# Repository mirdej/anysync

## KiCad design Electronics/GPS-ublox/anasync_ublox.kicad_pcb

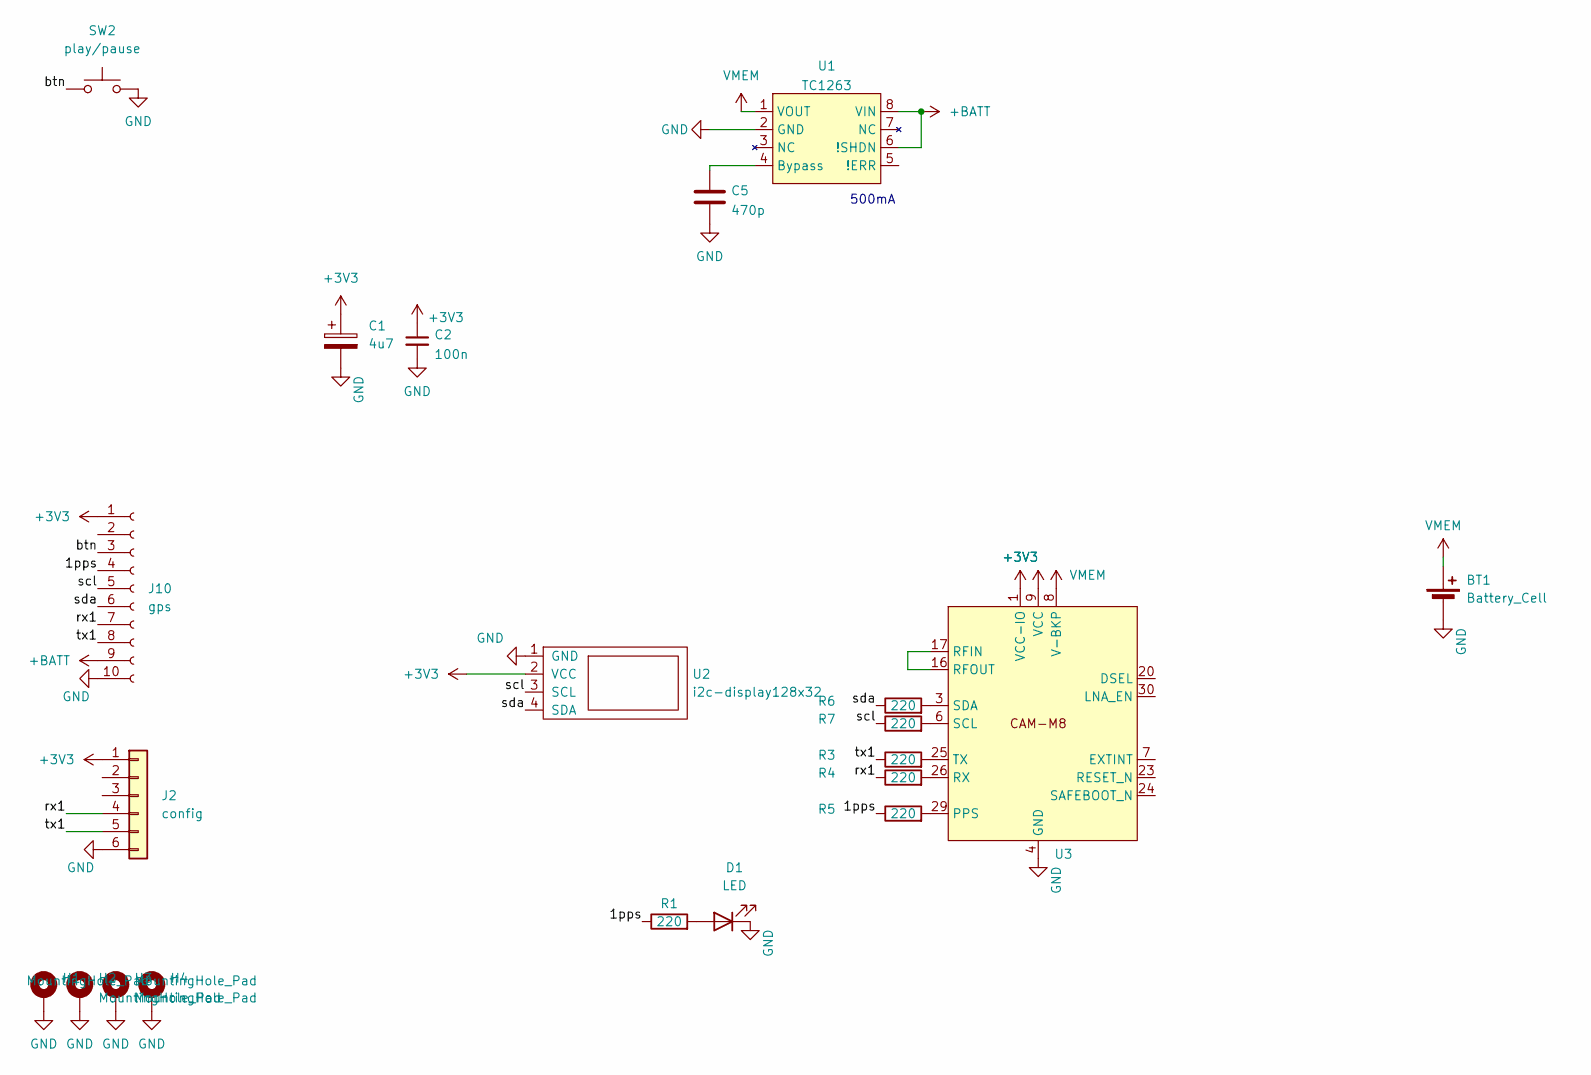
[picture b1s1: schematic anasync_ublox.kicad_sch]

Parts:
BT1: Battery_Cell; ComboPinhead_02
C1: 4u7; C_1206_3216Metric_Pad1.42x1.75mm_HandSolder
C2: 100n; C_0603_1608Metric_Pad1.05x0.95mm_HandSolder
C5: 470p; C_0805_2012Metric_Pad1.15x1.40mm_HandSolder
D1: LED; LED_D3.0mm_Clear
H1, H2, H3, H4: MountingHole_Pad; MountingHole_2.7mm_M2.5_DIN965_Pad
J2: config; ComboPinhead_06
J10: gps; ComboPinhead_10
R1, R3, R4, R5, R6, R7: 220; C_0805_2012Metric_Pad1.15x1.40mm_HandSolder
SW2: play/pause; Alps_Tactile_Switch
U1: TC1263; SOIC-8_3.9x4.9mm_P1.27mm
U2: i2c-display128x32; Bangood_I2C_Display
U3: CAM-M8

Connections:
+3V3: C1.1, C2.1, J2.1, J10.1, U2.2 (VCC), U3.1 (VCC-IO), U3.9 (VCC)
+BATT: J10.9, U1.6 (!SHDN), U1.8 (VIN)
/1pps: J10.4, R1.1, R5.1
/btn: J10.3, SW2.1
/rx1: J2.4, J10.7, R4.1
/scl: J10.5, R7.1, U2.3 (SCL)
/sda: J10.6, R6.1, U2.4 (SDA)
/tx1: J2.5, J10.8, R3.1
GND: BT1.2 (-), C1.2, C2.2, C5.2, D1.1 (K), H1.1, H2.1, H3.1, H4.1, J2.6, J10.10, SW2.2, U1.2 (GND), U2.1 (GND), U3.4 (GND), U3.5 (GND), U3.10 (GND), U3.11 (GND), U3.12 (GND), U3.13 (GND), U3.14 (GND), U3.15 (GND), U3.18 (GND), U3.19 (GND), U3.21 (GND), U3.22 (GND), U3.27 (GND), U3.31 (GND)
unnamed: D1.2 (A), R1.2
unnamed: C5.1, U1.4 (Bypass)
unnamed: R5.2, U3.29 (PPS)
unnamed: U3.16 (RFOUT), U3.17 (RFIN)
unnamed: R4.2, U3.26 (RX)
unnamed: R7.2, U3.6 (SCL)
unnamed: R6.2, U3.3 (SDA)
unnamed: R3.2, U3.25 (TX)
VMEM: BT1.1 (+), U1.1 (VOUT), U3.8 (V-BKP)

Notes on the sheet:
500mA

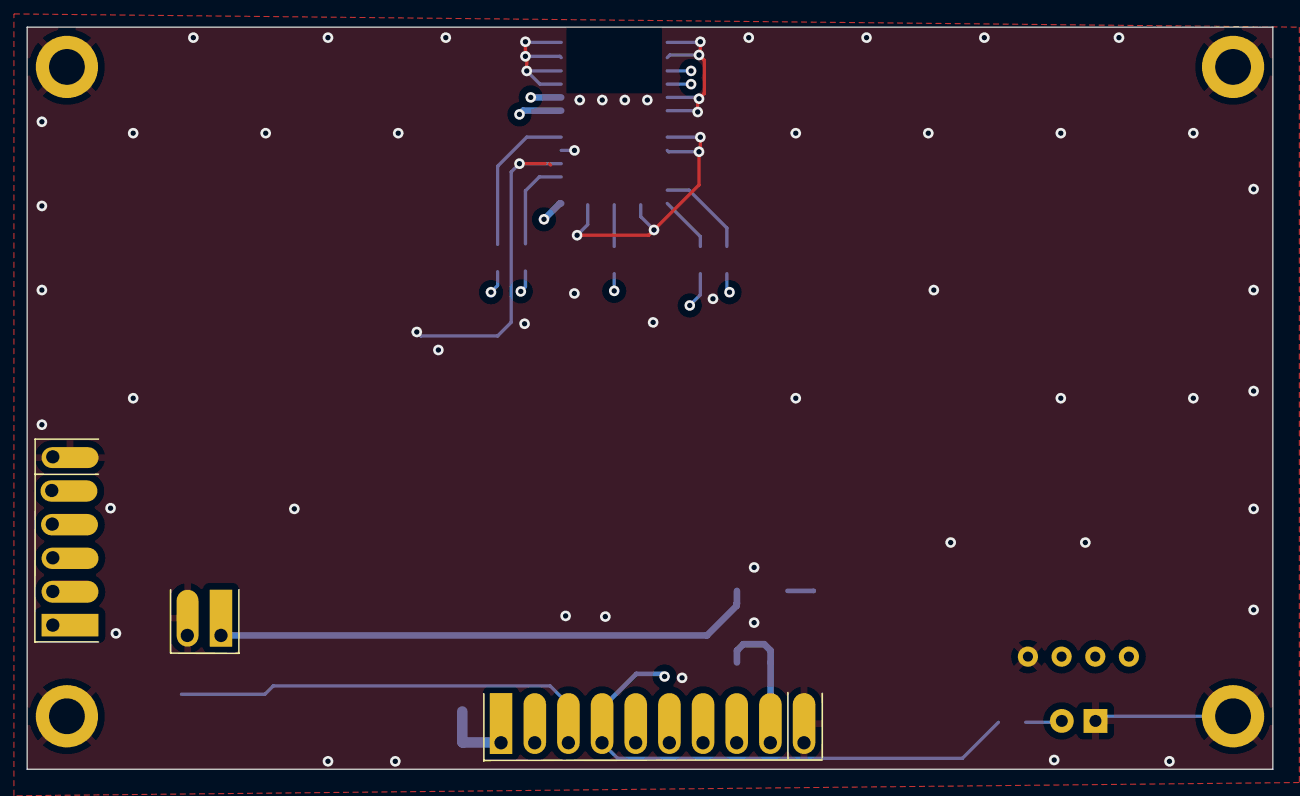
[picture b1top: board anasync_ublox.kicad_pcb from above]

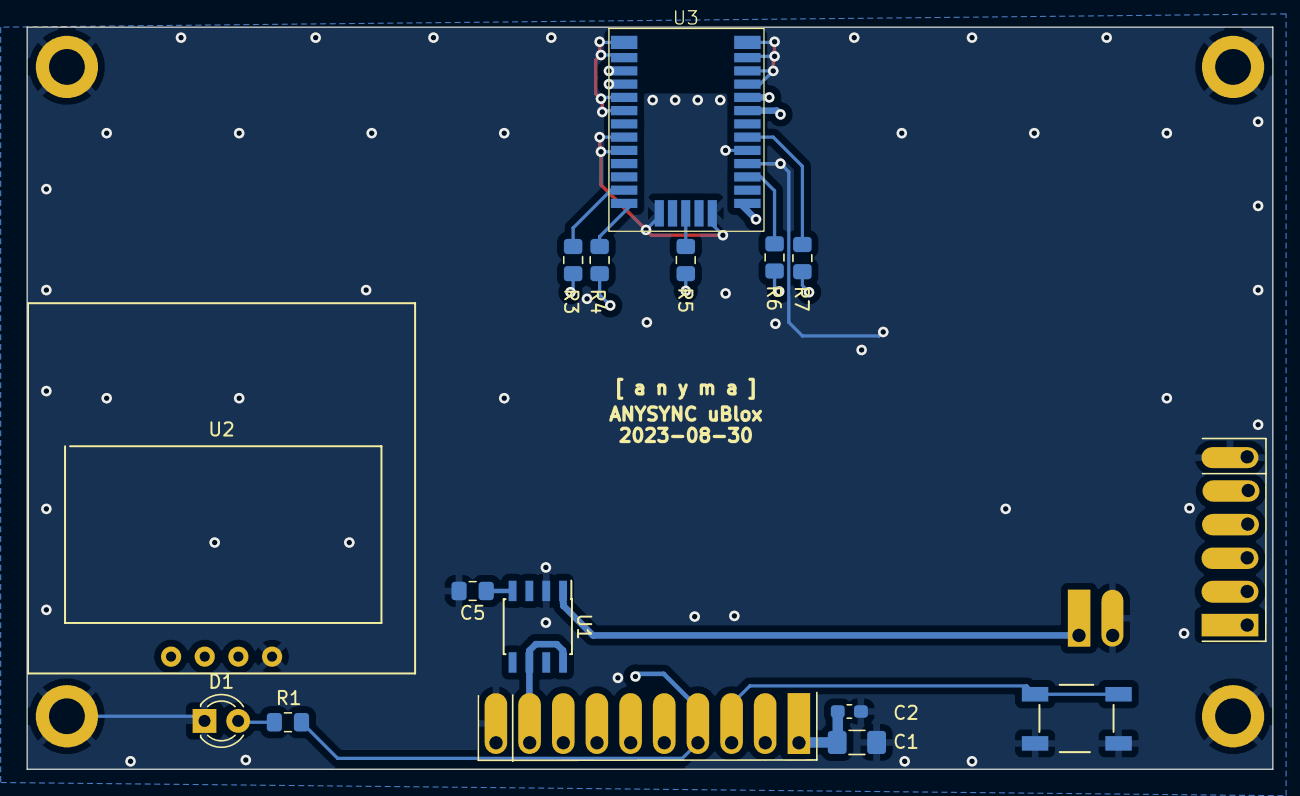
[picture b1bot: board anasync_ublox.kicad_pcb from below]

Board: 4 copper layers, 94.0 x 56.0 mm, 21 parts (15 on the bottom side), 18 nets.

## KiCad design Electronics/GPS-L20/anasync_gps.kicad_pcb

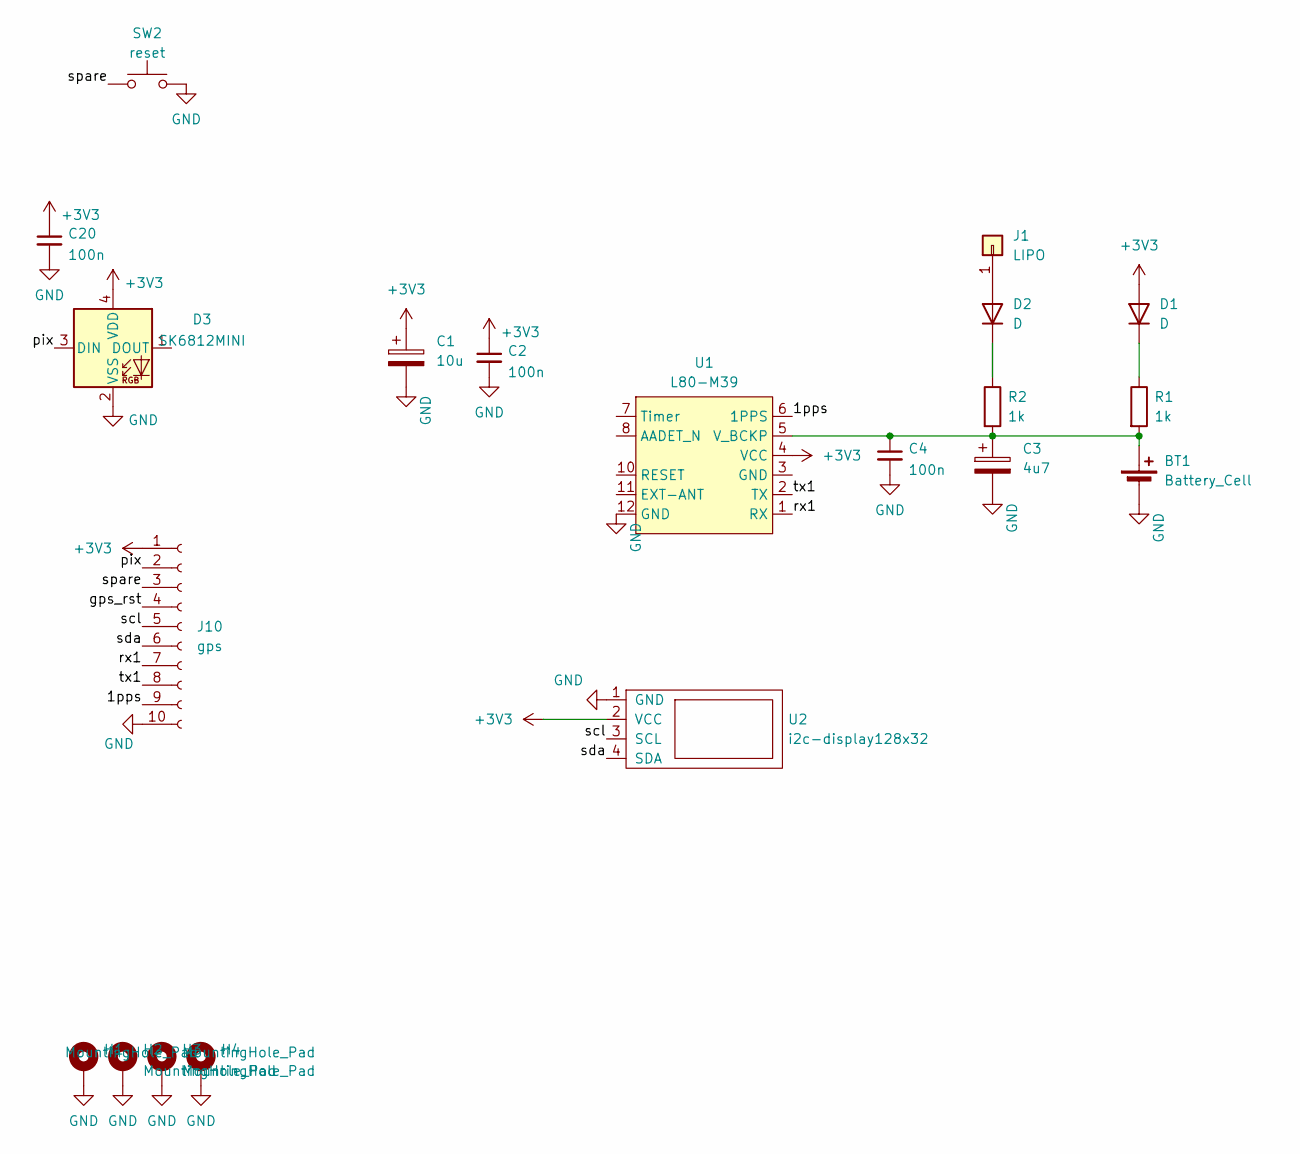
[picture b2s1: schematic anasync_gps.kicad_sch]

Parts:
BT1: Battery_Cell; smd-2pin
C1: 10u; C_1206_3216Metric_Pad1.42x1.75mm_HandSolder
C2, C4, C20: 100n; C_0603_1608Metric_Pad1.05x0.95mm_HandSolder
C3: 4u7; C_1206_3216Metric_Pad1.42x1.75mm_HandSolder
D1, D2: D; D_MiniMELF_Handsoldering
D3: SK6812MINI; SK6812-MINI-HS
H1, H2, H3, H4: MountingHole_Pad; MountingHole_2.2mm_M2_DIN965_Pad
J1: LIPO; smd-1pin
J10: gps; ComboPinhead_10
R1, R2: 1k; C_0805_2012Metric_Pad1.15x1.40mm_HandSolder
SW2: reset; Alps_Tactile_Switch
U1: L80-M39
U2: i2c-display128x32; Bangood_I2C_Display

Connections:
+3V3: C1.1, C2.1, C20.1, D1.2 (A), D3.4 (VDD), J10.1, U1.4 (VCC), U2.2 (VCC)
/1pps: J10.9, U1.6 (1PPS)
/gps_rst: J10.4
/pix: D3.3 (DIN), J10.2
/rx1: J10.7, U1.1 (RX)
/scl: J10.5, U2.3 (SCL)
/sda: J10.6, U2.4 (SDA)
/spare: J10.3, SW2.1
/tx1: J10.8, U1.2 (TX)
GND: BT1.2 (-), C1.2, C2.2, C3.2, C4.2, C20.2, D3.2 (VSS), H1.1, H2.1, H3.1, H4.1, J10.10, SW2.2, U1.12 (GND), U2.1 (GND)
unnamed: BT1.1 (+), C3.1, C4.1, R1.2, R2.2, U1.5 (V_BCKP)
unnamed: D1.1 (K), R1.1
unnamed: D2.2 (A), J1.1
unnamed: D2.1 (K), R2.1

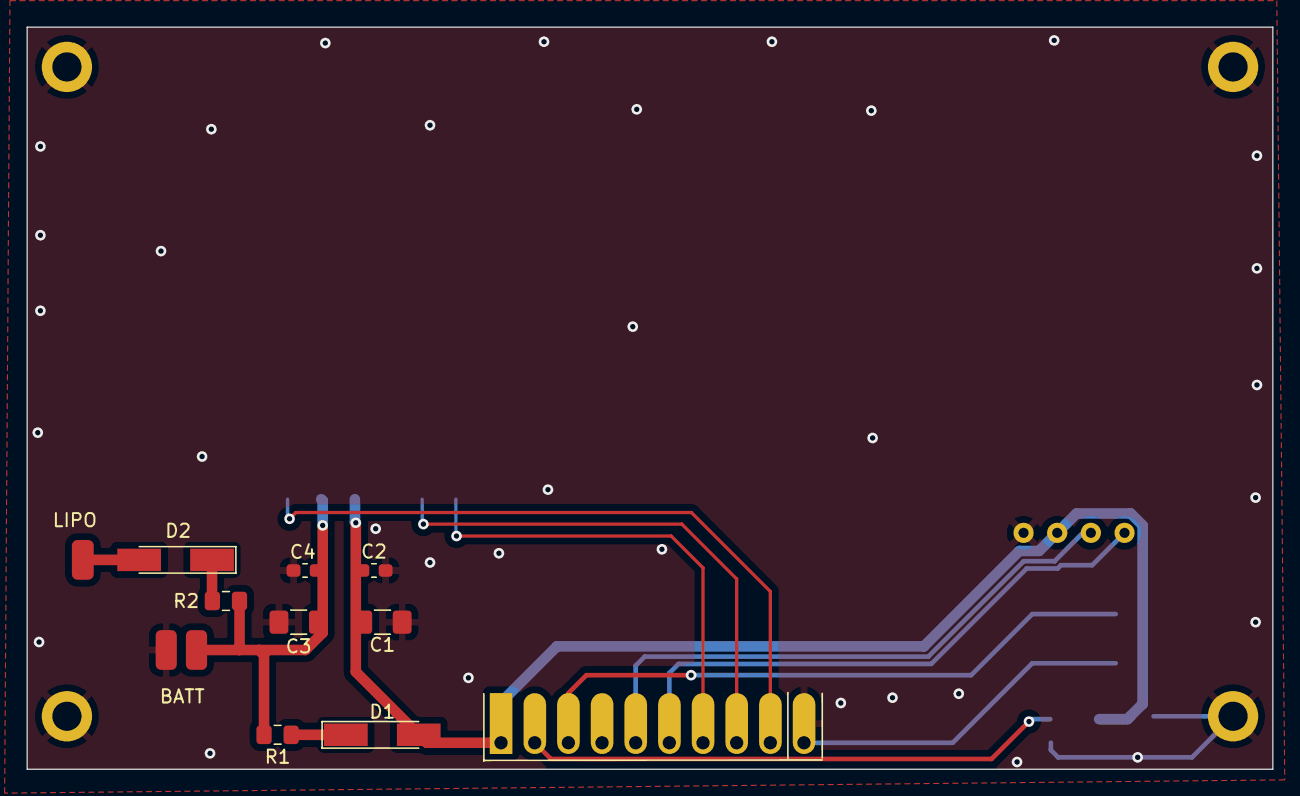
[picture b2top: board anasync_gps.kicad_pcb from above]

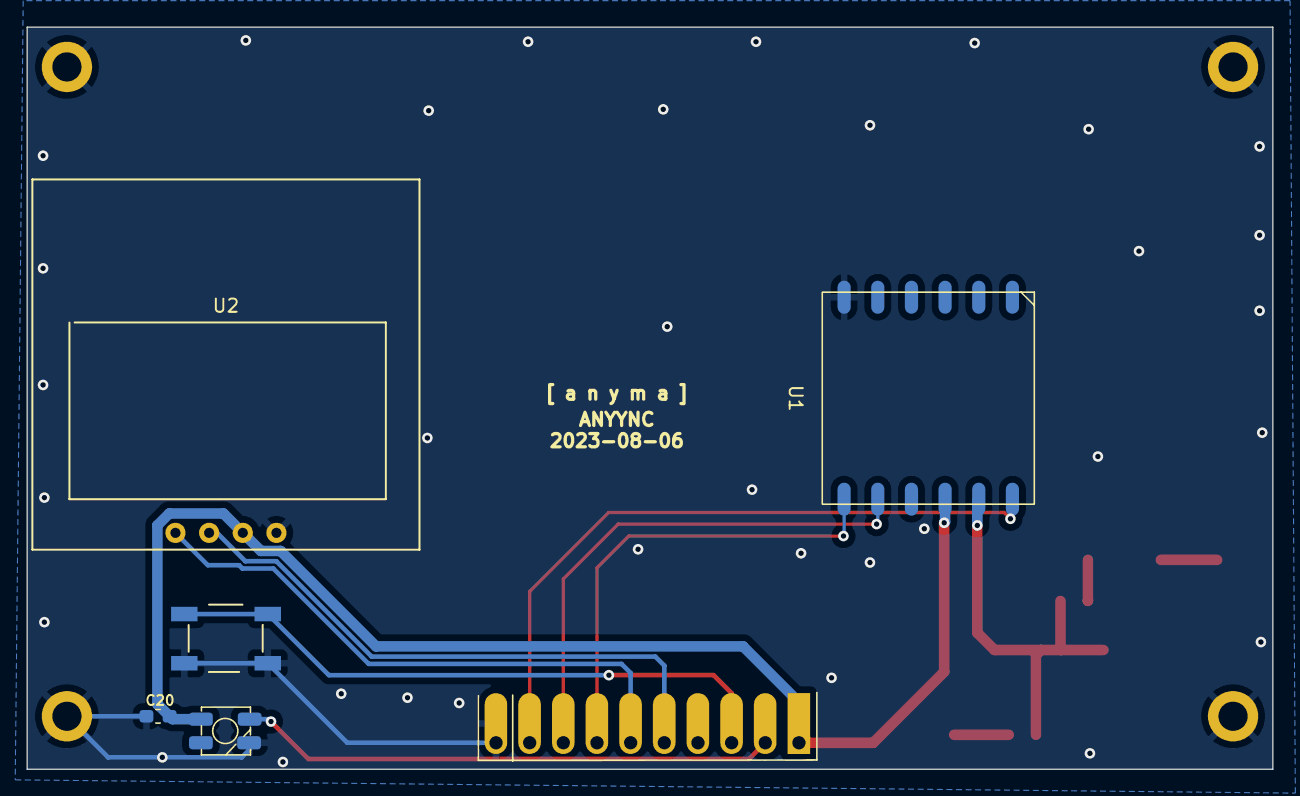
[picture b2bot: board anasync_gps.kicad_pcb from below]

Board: 2 copper layers, 94.0 x 56.0 mm, 20 parts (6 on the bottom side), 13 nets.

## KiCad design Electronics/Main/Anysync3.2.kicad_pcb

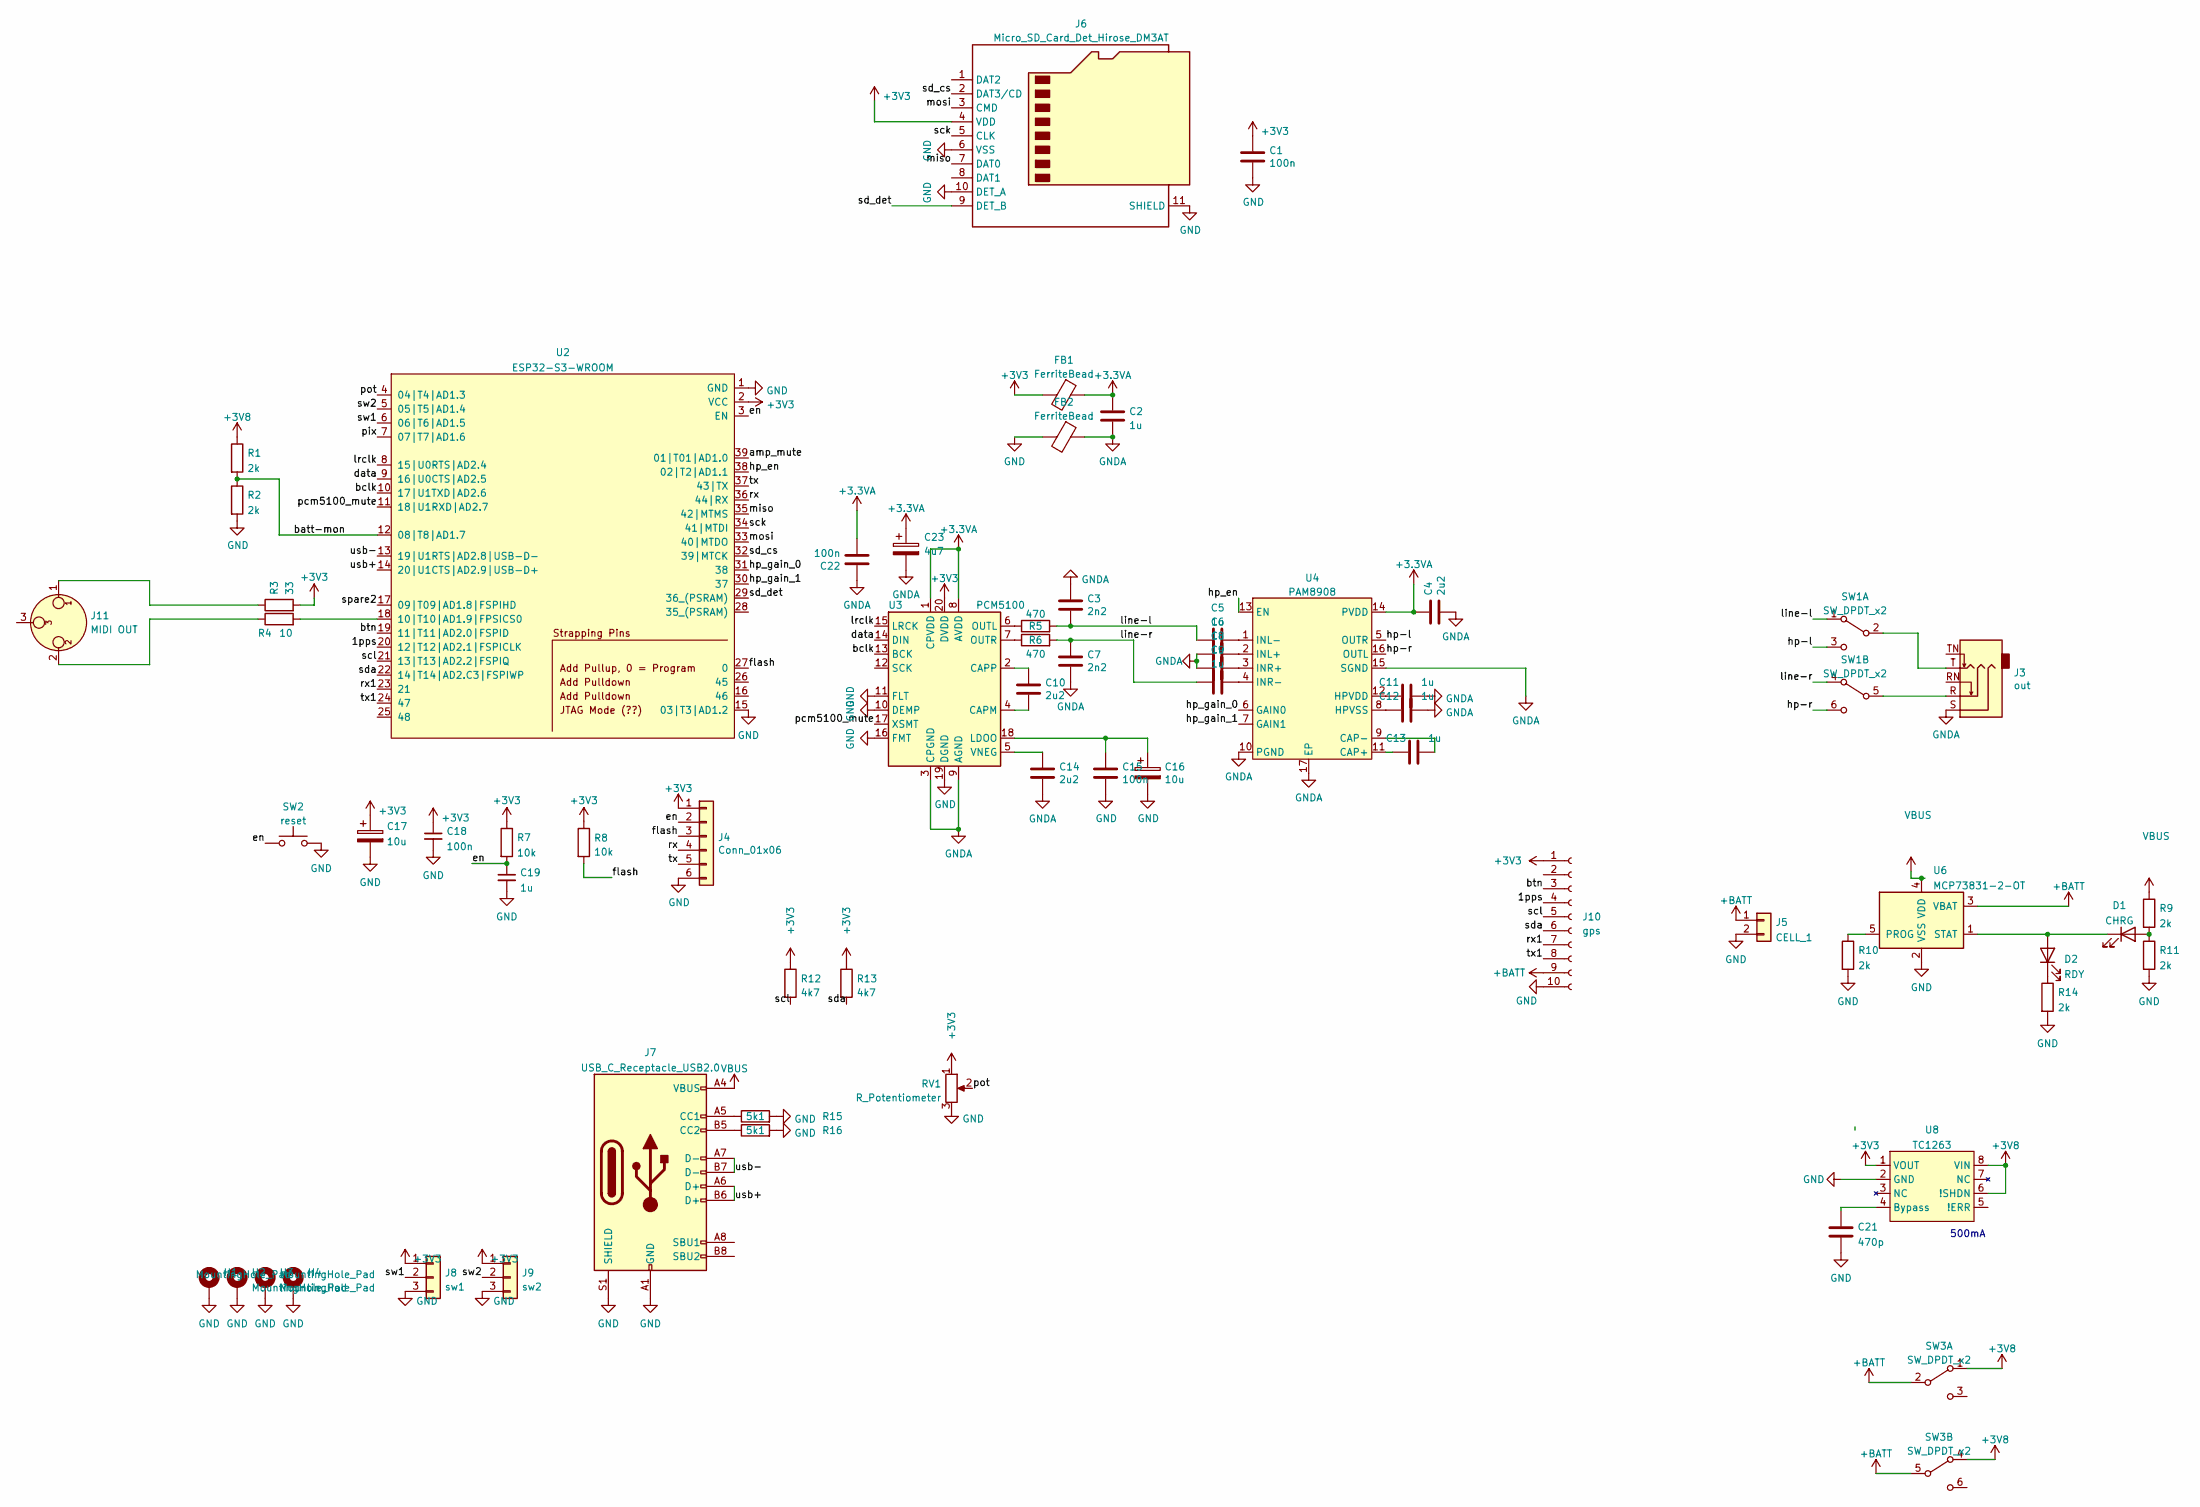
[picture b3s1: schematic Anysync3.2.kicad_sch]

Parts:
C1, C15, C18, C22: 100n; C_0603_1608Metric_Pad1.05x0.95mm_HandSolder
C2, C5, C6, C8, C9, C11, C12, C13, C19: 1u; C_0603_1608Metric_Pad1.05x0.95mm_HandSolder
C3, C7: 2n2; C_0805_2012Metric_Pad1.15x1.40mm_HandSolder
C4: 2u2; C_0805_2012Metric_Pad1.15x1.40mm_HandSolder
C10, C14: 2u2; C_1206_3216Metric_Pad1.42x1.75mm_HandSolder
C16: 10u; CP_EIA-3528-21_Kemet-B_Pad1.50x2.35mm_HandSolder
C17: 10u; C_1206_3216Metric_Pad1.42x1.75mm_HandSolder
C21: 470p; C_0805_2012Metric_Pad1.15x1.40mm_HandSolder
C23: 4u7; C_1206_3216Metric_Pad1.42x1.75mm_HandSolder
D1: CHRG; LED_0805_2012Metric
D2: RDY; LED_0805_2012Metric
FB1, FB2: FerriteBead; L_0805_2012Metric_Pad1.15x1.40mm_HandSolder
H1, H2, H3, H4: MountingHole_Pad; MountingHole_2.7mm_M2.5_DIN965_Pad
J3: out; Jack_3.5mm_SMD
J4: Conn_01x06; AnymaPOGO-ESP
J5: CELL_1; JST_XH_B2B-XH-AM_1x02_P2.50mm_Vertical
J6: Micro_SD_Card_Det_Hirose_DM3AT; microSD_HC_Hirose_DM3BT-DSF-PEJS
J7: USB_C_Receptacle_USB2.0; JAE_USB-C_SJ122205
J8: sw1; ComboPinhead_03
J9: sw2; ComboPinhead_03
J10: gps; ComboPinhead_10
J11: MIDI OUT; TRAPC3MSX
R1, R2, R9, R10, R11, R14: 2k; R_0805_2012Metric_Pad1.15x1.40mm_HandSolder
R3: 33; R_0805_2012Metric_Pad1.15x1.40mm_HandSolder
R4: 10; R_0805_2012Metric_Pad1.15x1.40mm_HandSolder
R5, R6: 470; R_0805_2012Metric_Pad1.15x1.40mm_HandSolder
R7, R8: 10k; R_0805_2012Metric_Pad1.15x1.40mm_HandSolder
R12, R13: 4k7; R_0805_2012Metric_Pad1.15x1.40mm_HandSolder
R15, R16: 5k1; R_0805_2012Metric_Pad1.15x1.40mm_HandSolder
RV1: R_Potentiometer; RK10J12E
SW1, SW3: SW_DPDT_x2; JS202011SCQN
SW2: reset; Alps_Tactile_Switch
U2: ESP32-S3-WROOM
U3: PCM5100; TSSOP-20_4.4x6.5mm_P0.65mm
U4: PAM8908; QFN-16-1EP_3x3mm_P0.5mm_EP1.7x1.7mm
U6: MCP73831-2-OT; SOT-23-5
U8: TC1263; SOIC-8_3.9x4.9mm_P1.27mm

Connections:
+3.3VA: C2.1, C4.1, C22.2, C23.1, FB1.1, U3.1 (CPVDD), U3.8 (AVDD), U4.14 (PVDD)
+3V3: C1.1, C17.1, C18.1, FB1.2, J4.1, J6.4 (VDD), J8.1, J9.1, J10.1, R3.2, R7.1, R8.1, R12.1, R13.1, RV1.1, U2.2 (VCC), U3.20 (DVDD), U8.1 (VOUT)
+3V8: R1.1, SW3.1 (A), SW3.4 (A), U8.6 (!SHDN), U8.8 (VIN)
+BATT: J5.1, J10.9, SW3.2 (B), SW3.5 (B), U6.3 (VBAT)
/1pps: J10.4, U2.20 (12|T12|AD2.1|FSPICLK)
/amp_mute: U2.39 (01|T01|AD1.0)
/batt-mon: R1.2, R2.1, U2.12 (08|T8|AD1.7)
/bclk: U2.10 (17|U1TXD|AD2.6), U3.13 (BCK)
/btn: J10.3, U2.19 (11|T11|AD2.0|FSPID)
/data: U2.9 (16|U0CTS|AD2.5), U3.14 (DIN)
/en: C19.1, J4.2, R7.2, SW2.1, U2.3 (EN)
/flash: J4.3, R8.2, U2.27 (0)
/hp-l: SW1.3 (C), U4.5 (OUTR)
/hp-r: SW1.6 (C), U4.16 (OUTL)
/hp_en: U2.38 (02|T2|AD1.1), U4.13 (EN)
/hp_gain_0: U2.31 (38), U4.6 (GAIN0)
/hp_gain_1: U2.30 (37), U4.7 (GAIN1)
/line-l: C3.2, C5.1, R5.2, SW1.1 (A)
/line-r: C7.1, C9.1, R6.2, SW1.4 (A)
/lrclk: U2.8 (15|U0RTS|AD2.4), U3.15 (LRCK)
/miso: J6.7 (DAT0), U2.35 (42|MTMS)
/mosi: J6.3 (CMD), U2.33 (40|MTDO)
/pcm5100_mute: U2.11 (18|U1RXD|AD2.7), U3.17 (XSMT)
/pix: U2.7 (07|T7|AD1.6)
/pot: RV1.2, U2.4 (04|T4|AD1.3)
/rx: J4.4, U2.36 (44|RX)
/rx1: J10.7, U2.23 (21)
/sck: J6.5 (CLK), U2.34 (41|MTDI)
/scl: J10.5, R12.2, U2.21 (13|T13|AD2.2|FSPIQ)
/sd_cs: J6.2 (DAT3/CD), U2.32 (39|MTCK)
/sd_det: J6.9 (DET_B), U2.29 (36_(PSRAM))
/sda: J10.6, R13.2, U2.22 (14|T14|AD2.C3|FSPIWP)
/spare2: U2.17 (09|T09|AD1.8|FSPIHD)
/sw1: J8.2, U2.6 (06|T6|AD1.5)
/sw2: J9.2, U2.5 (05|T5|AD1.4)
/tx: J4.5, U2.37 (43|TX)
/tx1: J10.8, U2.24 (47)
/usb+: J7.A6 (D+), J7.B6 (D+), U2.14 (20|U1CTS|AD2.9|USB-D+)
/usb-: J7.A7 (D-), J7.B7 (D-), U2.13 (19|U1RTS|AD2.8|USB-D-)
GND: C1.2, C15.2, C16.2, C17.2, C18.2, C19.2, C21.2, FB2.2, H1.1, H2.1, H3.1, H4.1, J4.6, J5.2, J6.6 (VSS), J6.10 (DET_A), J6.11 (SHIELD), J7.A1 (GND), J7.A12 (GND), J7.B1 (GND), J7.B12 (GND), J7.S1 (SHIELD), J8.3, J9.3, J10.10, R2.2, R10.2, R11.2, R14.2, R15.2, R16.2, RV1.3, SW2.2, U2.1 (GND), U2.15 (03|T3|AD1.2), U2.40 (GND), U2.41 (GND), U3.10 (DEMP), U3.11 (FLT), U3.16 (FMT), U3.19 (DGND), U6.2 (VSS), U8.2 (GND)
GNDA: C2.2, C3.1, C4.2, C6.1, C7.2, C8.1, C11.2, C12.2, C14.2, C22.1, C23.2, FB2.1, J3.S, U3.3 (CPGND), U3.9 (AGND), U4.10 (PGND), U4.15 (SGND), U4.17 (EP)
unnamed: D1.2 (A), R9.2, R11.1
unnamed: D1.1 (K), D2.2 (A), U6.1 (STAT)
unnamed: D2.1 (K), R14.1
unnamed: J7.A5 (CC1), R15.1
unnamed: J7.B5 (CC2), R16.1
unnamed: J11.1, R3.1
unnamed: J11.2, R4.1
unnamed: J3.T, SW1.2 (B)
unnamed: J3.R, SW1.5 (B)
unnamed: R4.2, U2.18 (10|T10|AD1.9|FPSICS0)
unnamed: C10.2, U3.4 (CAPM)
unnamed: C10.1, U3.2 (CAPP)
unnamed: C15.1, C16.1, U3.18 (LDOO)
unnamed: R5.1, U3.6 (OUTL)
unnamed: R6.1, U3.7 (OUTR)
unnamed: C14.1, U3.5 (VNEG)
unnamed: C13.1, U4.11 (CAP+)
unnamed: C13.2, U4.9 (CAP-)
unnamed: C11.1, U4.12 (HPVDD)
unnamed: C12.1, U4.8 (HPVSS)
unnamed: C6.2, U4.2 (INL+)
unnamed: C5.2, U4.1 (INL-)
unnamed: C8.2, U4.3 (INR+)
unnamed: C9.2, U4.4 (INR-)
unnamed: R10.1, U6.5 (PROG)
unnamed: C21.1, U8.4 (Bypass)
VBUS: J7.A4 (VBUS), J7.A9 (VBUS), J7.B4 (VBUS), J7.B9 (VBUS), R9.1, U6.4 (VDD)

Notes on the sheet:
500mA

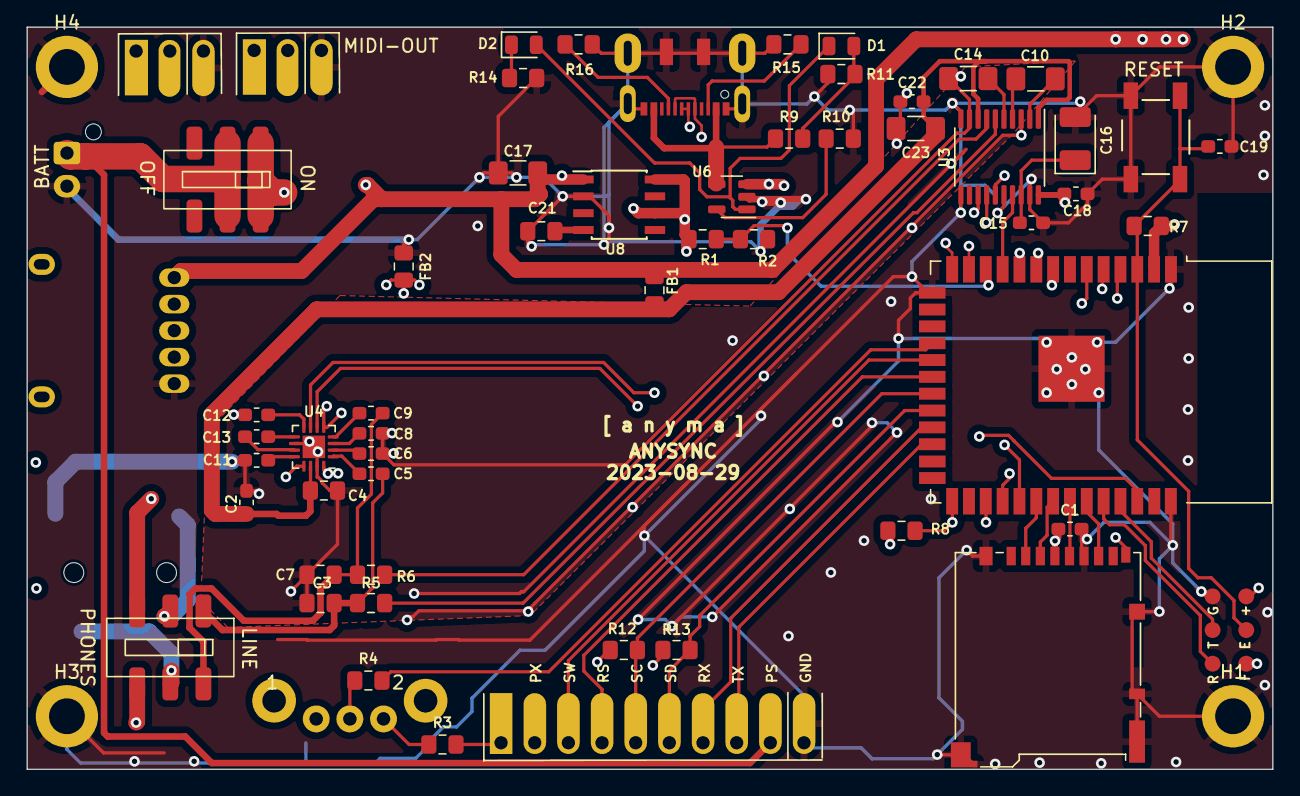
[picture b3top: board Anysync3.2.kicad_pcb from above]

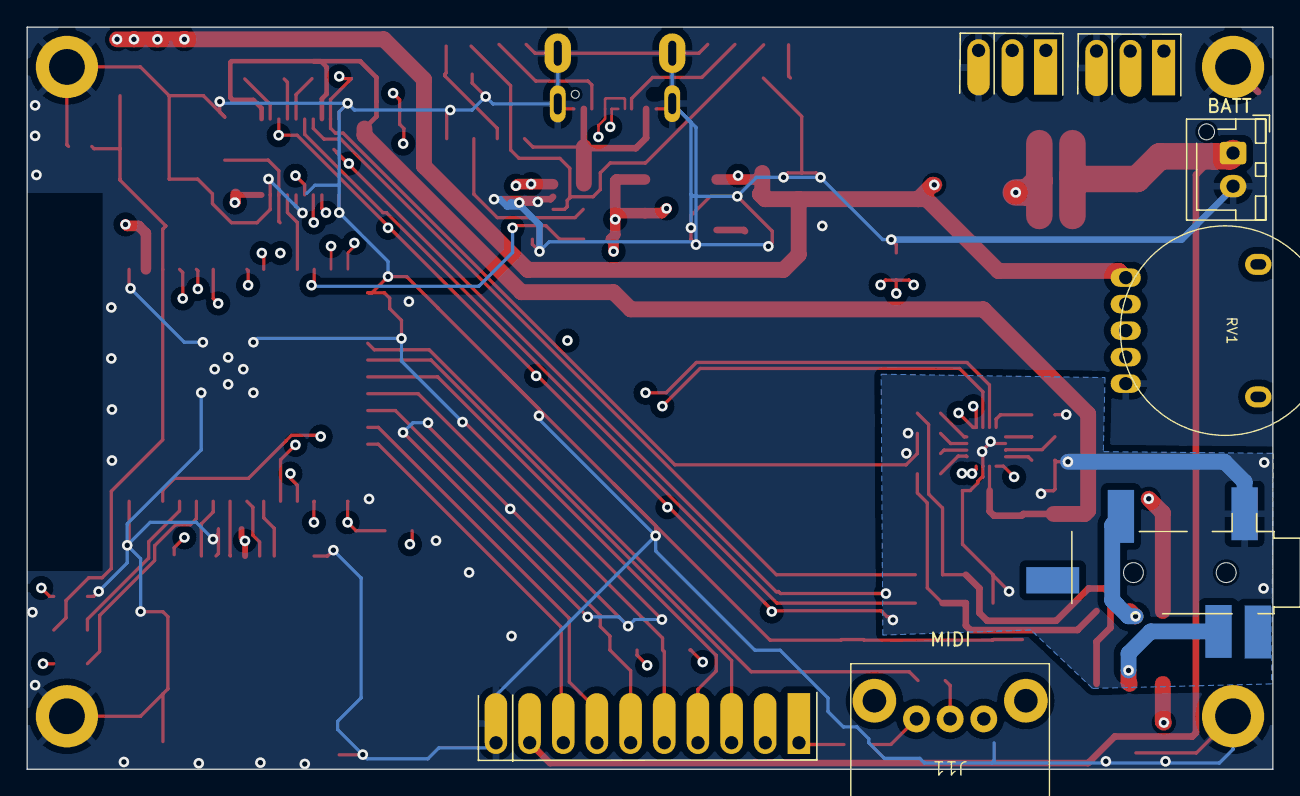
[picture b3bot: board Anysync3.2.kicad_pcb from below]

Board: 4 copper layers, 94.0 x 56.0 mm, 64 parts (5 on the bottom side), 65 nets.

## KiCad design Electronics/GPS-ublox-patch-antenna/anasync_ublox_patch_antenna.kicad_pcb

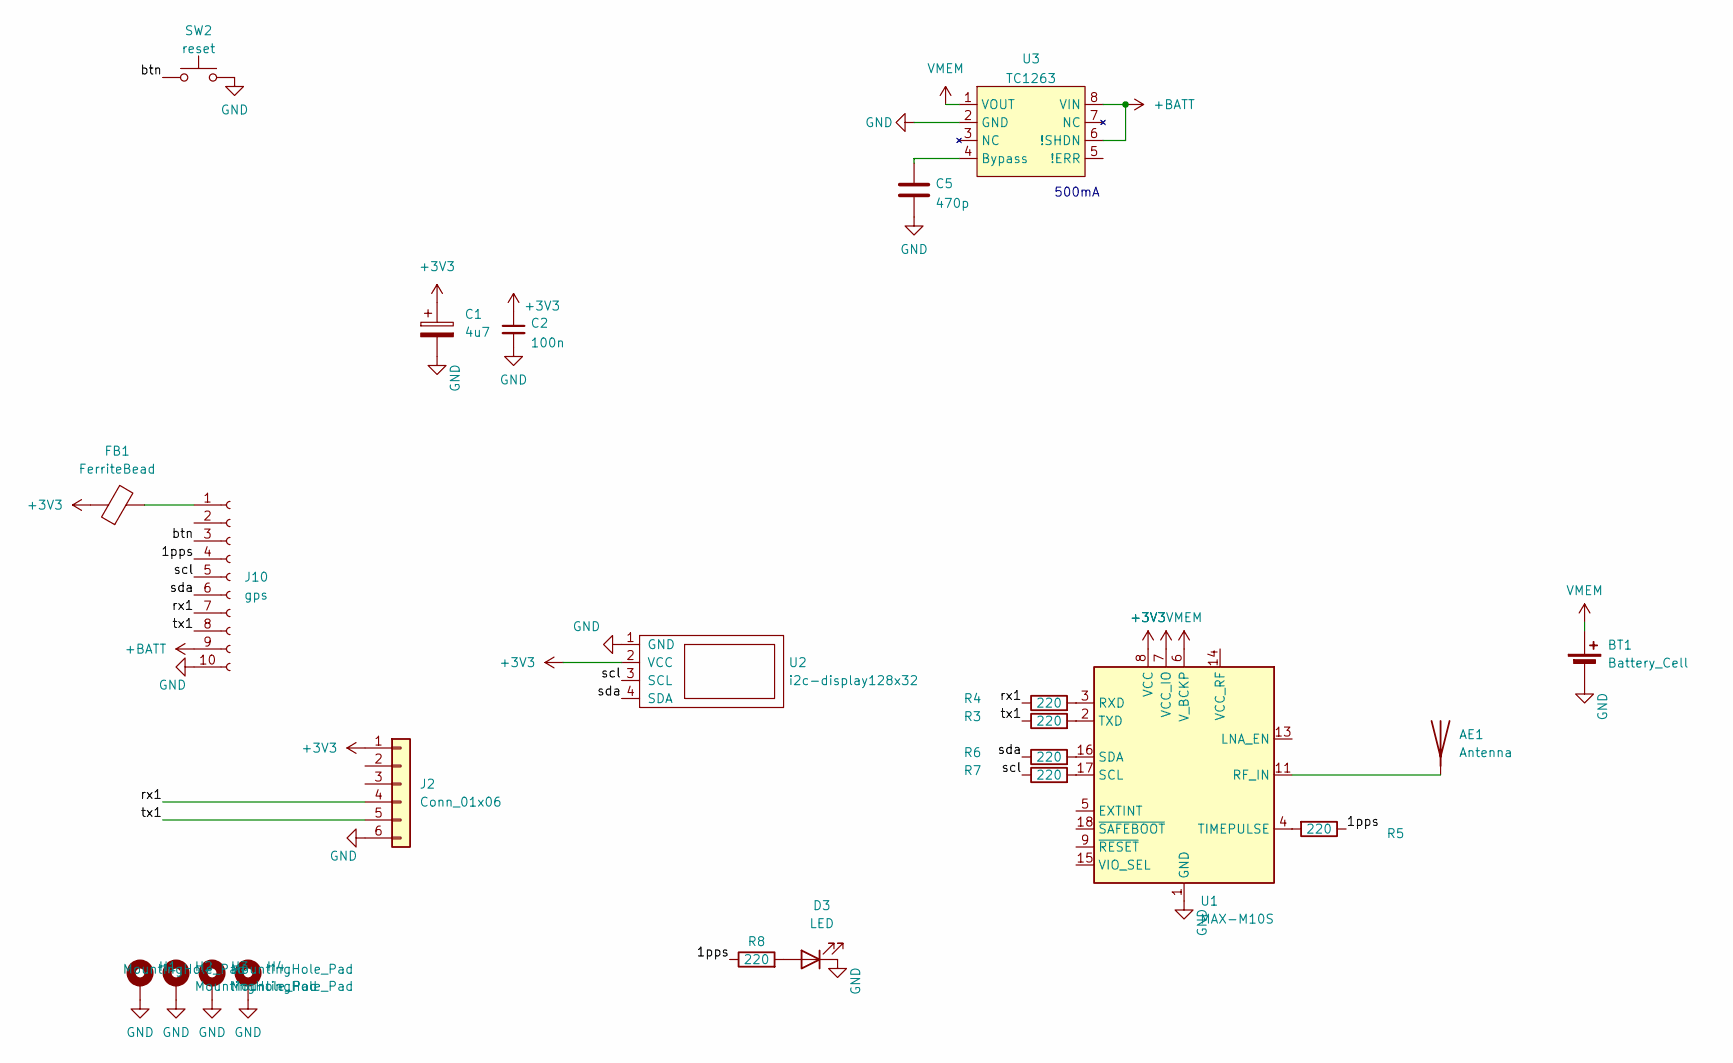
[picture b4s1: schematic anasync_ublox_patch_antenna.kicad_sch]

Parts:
AE1: Antenna; 25x25-patch-antenna
BT1: Battery_Cell; ComboPinhead_02
C1: 4u7; C_1206_3216Metric_Pad1.42x1.75mm_HandSolder
C2: 100n; C_0603_1608Metric_Pad1.05x0.95mm_HandSolder
C5: 470p; C_0805_2012Metric_Pad1.15x1.40mm_HandSolder
D3: LED; LED_D3.0mm_Clear
FB1: FerriteBead; L_0805_2012Metric_Pad1.15x1.40mm_HandSolder
H1, H2, H3, H4: MountingHole_Pad; MountingHole_2.7mm_M2.5_DIN965_Pad
J2: Conn_01x06; PinHeader_1x06_P2.54mm_Vertical
J10: gps; PinHeader_1x10_P2.54mm_Vertical
R3, R4, R5, R6, R7, R8: 220; C_0805_2012Metric_Pad1.15x1.40mm_HandSolder
SW2: reset; Alps_Tactile_Switch
U1: MAX-M10S; ublox_MAX
U2: i2c-display128x32; Bangood_I2C_Display
U3: TC1263; SOIC-8_3.9x4.9mm_P1.27mm

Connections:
+3V3: C1.1, C2.1, FB1.1, J2.1, U1.7 (VCC_IO), U1.8 (VCC), U2.2 (VCC)
+BATT: J10.9, U3.6 (!SHDN), U3.8 (VIN)
/1pps: J10.4, R5.1, R8.1
/btn: J10.3, SW2.1
/rx1: J2.4, J10.7, R4.1
/scl: J10.5, R7.1, U2.3 (SCL)
/sda: J10.6, R6.1, U2.4 (SDA)
/tx1: J2.5, J10.8, R3.1
GND: BT1.2 (-), C1.2, C2.2, C5.2, D3.1 (K), H1.1, H2.1, H3.1, H4.1, J2.6, J10.10, SW2.2, U1.1 (GND), U1.10 (GND), U1.12 (GND), U2.1 (GND), U3.2 (GND)
unnamed: AE1.1 (A), U1.11 (RF_IN)
unnamed: D3.2 (A), R8.2
unnamed: FB1.2, J10.1
unnamed: R4.2, U1.3 (RXD)
unnamed: R7.2, U1.17 (SCL)
unnamed: R6.2, U1.16 (SDA)
unnamed: R5.2, U1.4 (TIMEPULSE)
unnamed: R3.2, U1.2 (TXD)
unnamed: C5.1, U3.4 (Bypass)
VMEM: BT1.1 (+), U1.6 (V_BCKP), U3.1 (VOUT)

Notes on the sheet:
500mA

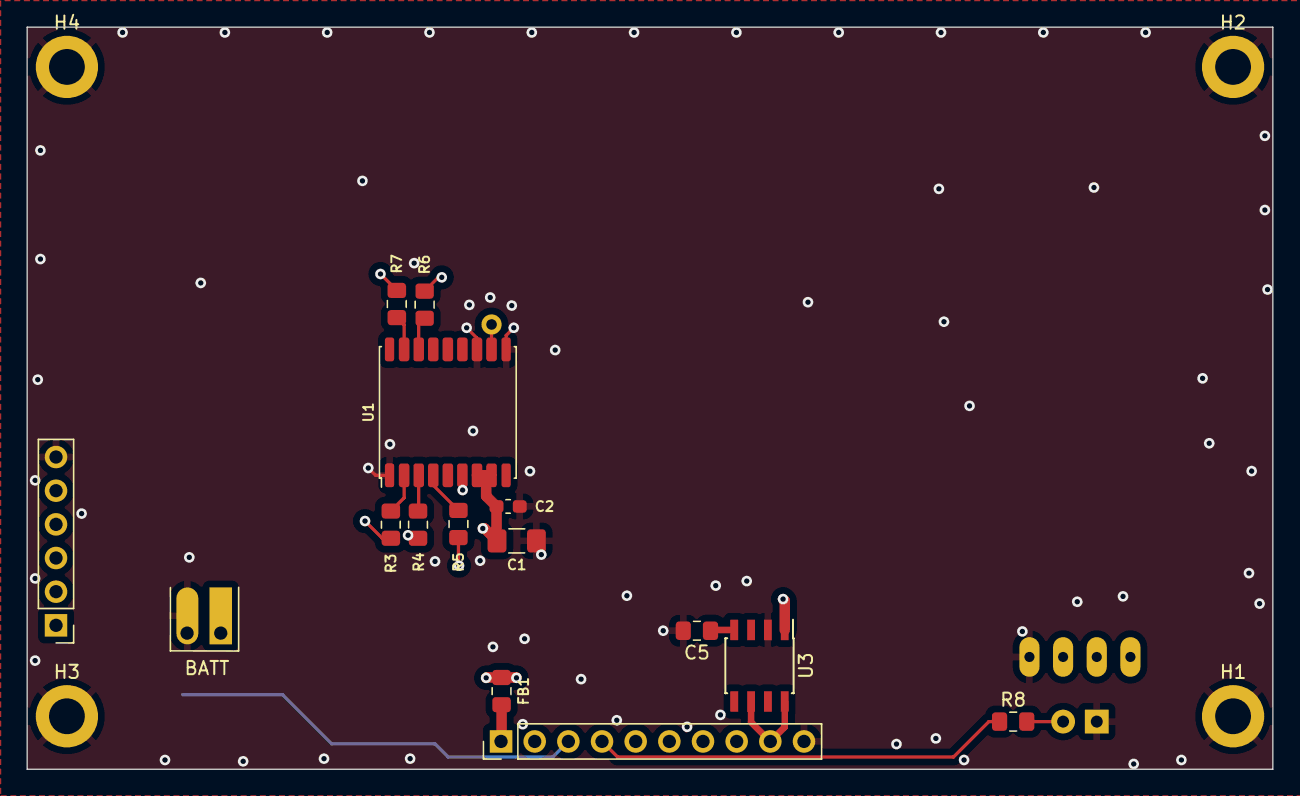
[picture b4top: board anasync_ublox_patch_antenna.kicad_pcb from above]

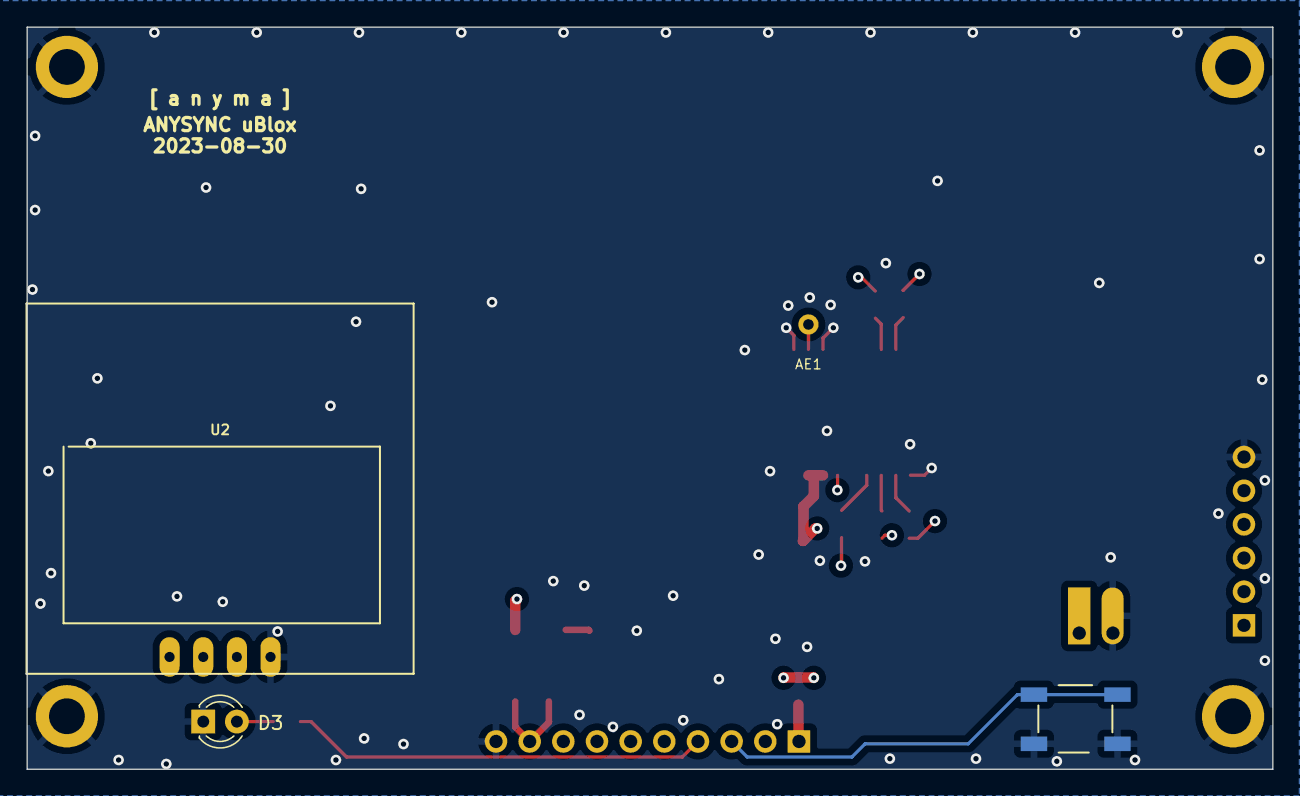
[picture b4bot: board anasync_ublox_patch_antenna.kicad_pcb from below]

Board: 4 copper layers, 94.0 x 56.0 mm, 23 parts (4 on the bottom side), 19 nets.

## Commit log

2023-08-13 own clock
2023-08-14 change interrupt pin
2023-08-14 inorporate code from ESP32-GPS-msec-ts.ino
2023-08-14 cleanup
2023-08-15 clean
2023-08-15 can remove amd insert sd-card
2023-08-15 add display
2023-08-15 add midifile parser
2023-08-15 add sync_file from versionn1
2023-08-15 Add syncfile, mod for SD.h
2023-08-15 syncfile, audio erratic
2023-08-16 read show start from config
2023-08-16 refactor code with less tasks
2023-08-16 midi only test
2023-08-16 remove queuebased comm with audio task
2023-08-16 not so bad
2023-08-17 fix show_end? fix reset on insert card?
2023-08-17 try to find memory leak, disable wifi
2023-08-17 fix memory leak. fix display issues
2023-08-18 debug output on both pins
2023-08-25 start exactly on the second. try to get tighter audio play
2023-08-31 set rtc offset in parsehowfile, defult to 7200
2023-08-31 rtc offest in show file
2023-08-31 use gps rtc if avalable while waiting for fix
2023-08-31 more robust file handing
2023-08-31 fix bug when using play button
2023-08-31 wild guess to get gps_rtc time setting more accurate
2023-08-31 dont parse show file
2023-08-31 Download show on start
2023-08-31 periodically downlowd json
2023-09-10 can change sever in config.json
2023-09-10 check file version, download on change only
2023-09-10 send showversion for update verification
2023-09-16 bigger json doc size
2024-05-09 pullup on miso
2024-05-09 Move to subfolder
2024-05-09 add electronics
